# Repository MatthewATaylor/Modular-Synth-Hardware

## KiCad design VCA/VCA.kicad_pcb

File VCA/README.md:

# VCA

A simple dual VCA based on [the similar Yusynth design](http://yusynth.net/Modular/EN/VCA/index.html), including both a Eurorack level and line level output.

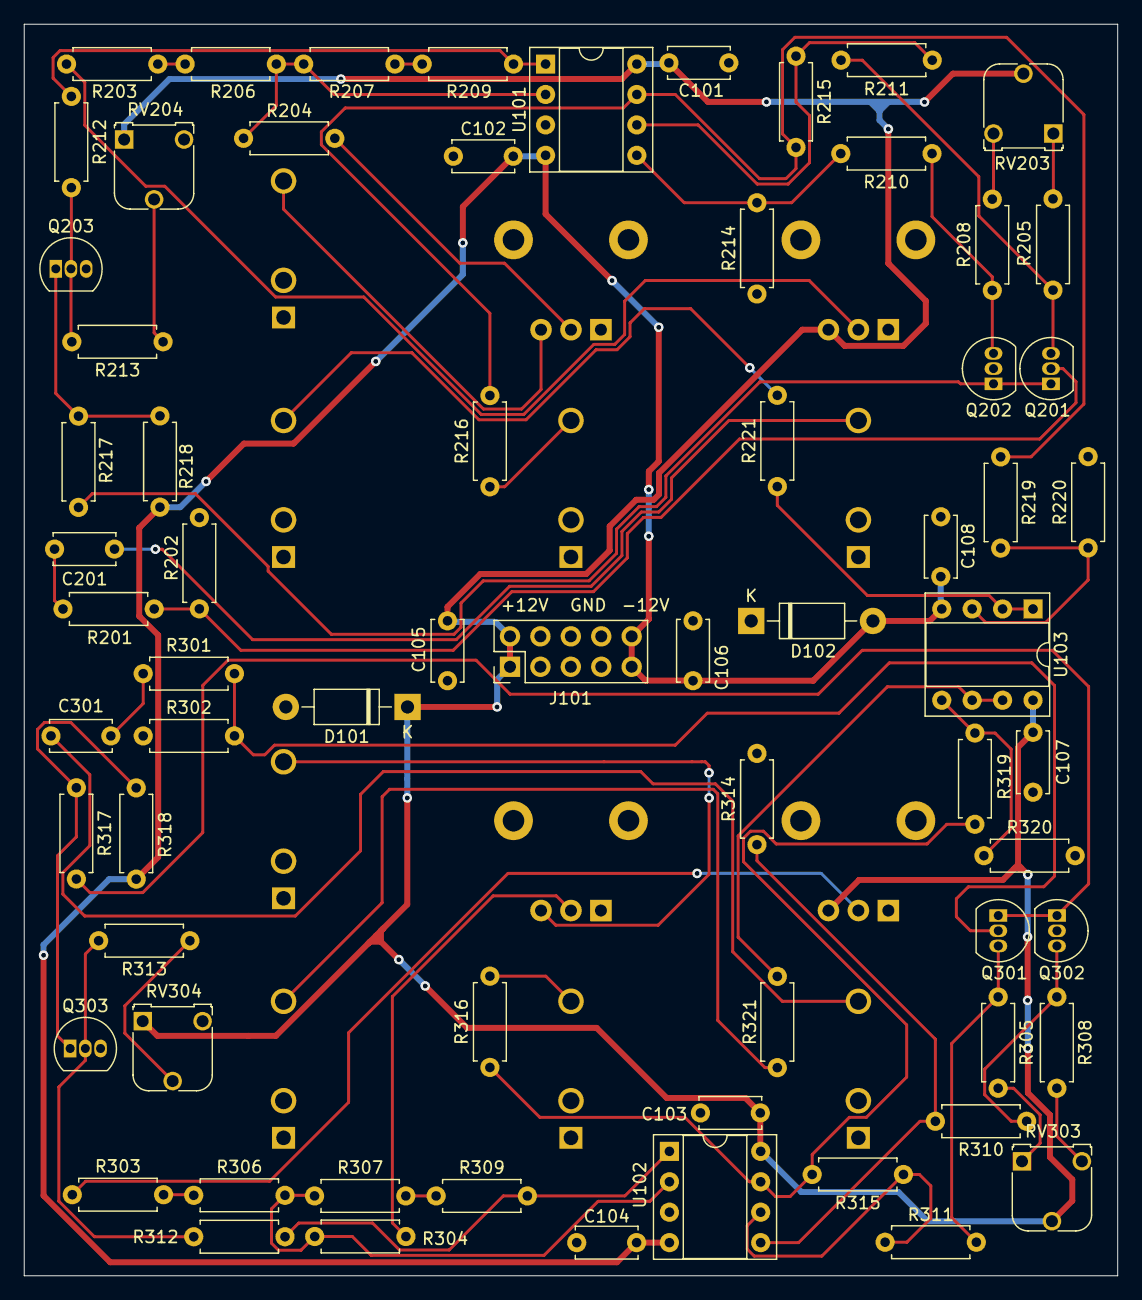
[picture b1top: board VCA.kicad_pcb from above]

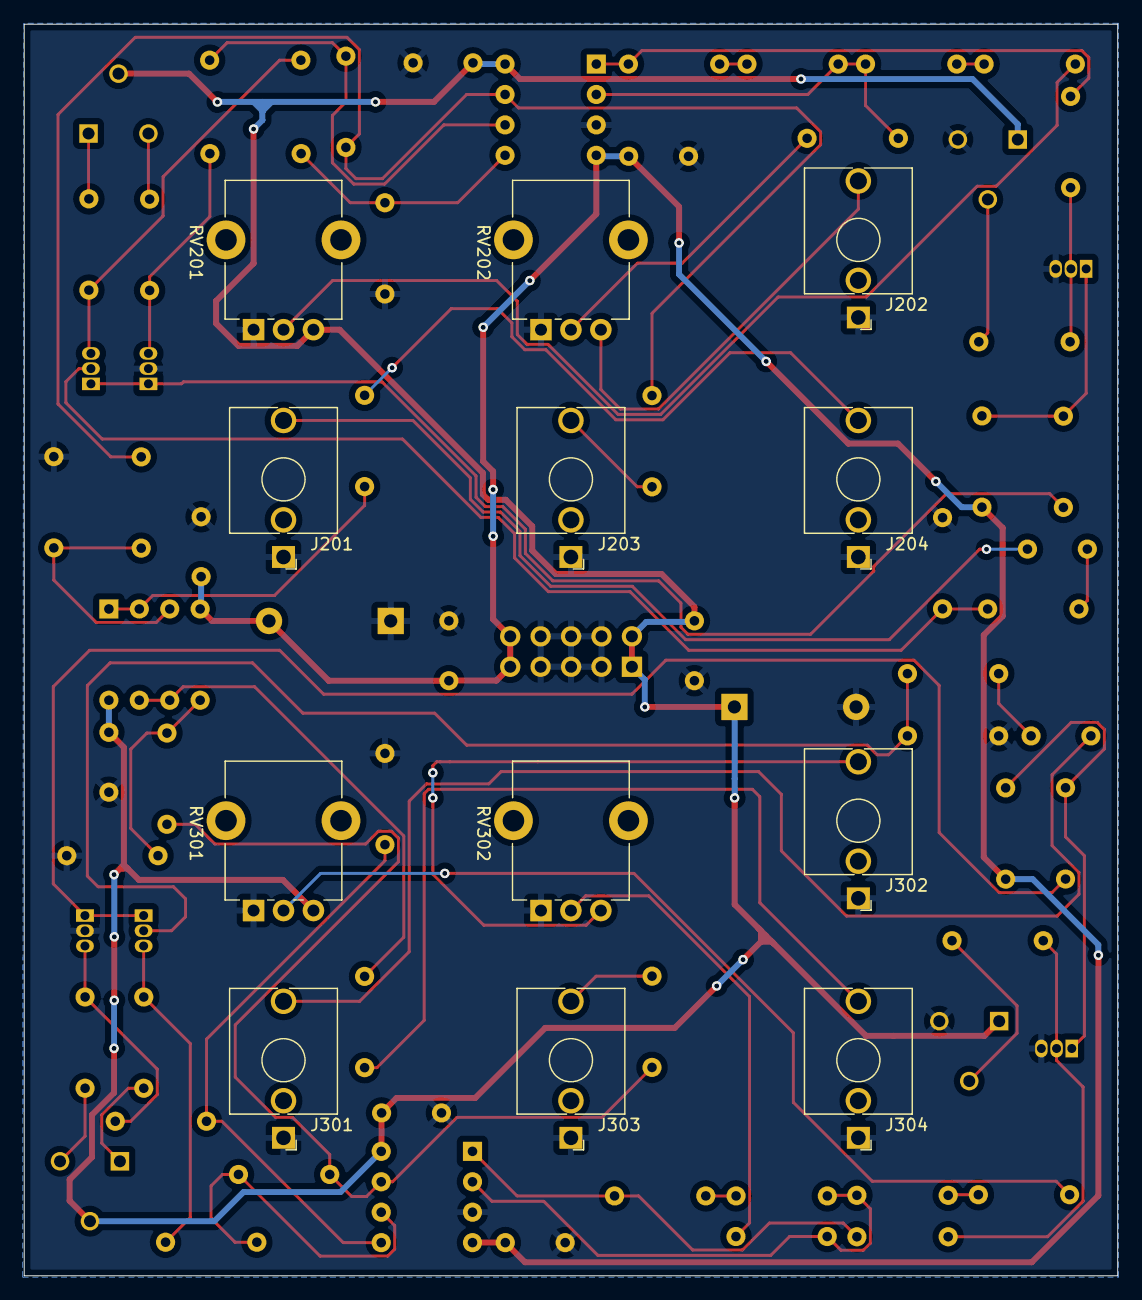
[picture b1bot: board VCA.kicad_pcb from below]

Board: 2 copper layers, 91.3 x 104.5 mm, 80 parts (12 on the bottom side), 53 nets.

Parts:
C101, C102, C103, C104, C107, C108: 10n; C_Disc_D5.0mm_W2.5mm_P5.00mm
C105, C106: 0.1u; C_Disc_D5.0mm_W2.5mm_P5.00mm
C201, C301: 10u; C_Disc_D5.0mm_W2.5mm_P5.00mm
D101, D102: 1N5819; D_DO-41_SOD81_P10.16mm_Horizontal
J101: Conn_02x05_Odd_Even; PinHeader_2x05_P2.54mm_Vertical
J201, J202, J203, J204, J301, J302, J303, J304: AudioJack2_SwitchT; Jack_3.5mm_QingPu_WQP-PJ398SM_Vertical_CircularHoles
Q201, Q202, Q203, Q301, Q302, Q303: 2N3904; TO-92_Inline
R201, R203, R301, R303: 220k; R_Axial_DIN0207_L6.3mm_D2.5mm_P7.62mm_Horizontal
R202, R216, R221, R302, R316, R321: 1k; R_Axial_DIN0207_L6.3mm_D2.5mm_P7.62mm_Horizontal
R204, R304: 470k; R_Axial_DIN0207_L6.3mm_D2.5mm_P7.62mm_Horizontal
R205, R208, R305, R308: 150k; R_Axial_DIN0207_L6.3mm_D2.5mm_P7.62mm_Horizontal
R206, R214, R215, R306, R314, R315: 330k; R_Axial_DIN0207_L6.3mm_D2.5mm_P7.62mm_Horizontal
R207, R307: 100k; R_Axial_DIN0207_L6.3mm_D2.5mm_P7.62mm_Horizontal
R209, R212, R213, R217, R309, R312, R313, R317: 22k; R_Axial_DIN0207_L6.3mm_D2.5mm_P7.62mm_Horizontal
R210, R211, R218, R310, R311, R318: 10k; R_Axial_DIN0207_L6.3mm_D2.5mm_P7.62mm_Horizontal
R219, R319: 5.6k; R_Axial_DIN0207_L6.3mm_D2.5mm_P7.62mm_Horizontal
R220, R320: 1.5k; R_Axial_DIN0207_L6.3mm_D2.5mm_P7.62mm_Horizontal
RV201, RV202, RV301, RV302: 50k; Potentiometer_Alpha_RD901F-40-00D_Single_Vertical_CircularH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
RV203, RV204, RV303, RV304: 10k; Potentiometer_Runtron_RM-065_Vertical
U101, U102, U103: TL072; DIP-8_W7.62mm_Socket

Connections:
+12V: C101.1, C103.1, C105.1, C107.1, D101.1 (K), J101.1, J101.2, RV201.3, RV203.2, RV204.1, RV301.3, RV303.2, RV304.1, U101.8 (V+), U102.8 (V+), U103.8 (V+)
-12V: C102.1, C104.1, C106.2, C108.1, D102.2 (A), J101.9, J101.10, R218.1, R318.1, U101.4 (V-), U102.4 (V-), U103.4 (V-)
GND: C101.2, C102.2, C103.2, C104.2, C105.2, C106.1, C107.2, C108.2, D101.2 (A), D102.1 (K), J101.3, J101.4, J101.5, J101.6, J101.7, J101.8, J201.S, J202.S, J203.S, J204.S, J301.S, J302.S, J303.S, J304.S, Q202.2 (B), Q203.3 (C), Q302.2 (B), Q303.3 (C), R202.1, R214.2, R220.2, R302.1, R314.2, R320.2, RV201.1, RV202.1, RV204.3, RV301.1, RV302.1, RV304.3, U101.3 (+), U102.3 (+)
unnamed: C201.1, J201.T
unnamed: C201.2, R201.1
unnamed: C301.1, J301.T
unnamed: C301.2, R301.1
unnamed: J202.T, RV202.3
unnamed: J203.T, R216.2
unnamed: J204.T, R221.2
unnamed: J302.T, RV302.3
unnamed: J303.T, R316.2
unnamed: J304.T, R321.2
unnamed: Q201.1 (E), Q202.1 (E), R217.2
unnamed: Q201.2 (B), R201.2, R202.2
unnamed: Q201.3 (C), R205.1, R211.1
unnamed: Q202.3 (C), R208.1, R210.1
unnamed: Q203.1 (E), R217.1, R218.2
unnamed: Q203.2 (B), R212.2, R213.2
unnamed: Q301.1 (E), Q302.1 (E), R317.2
unnamed: Q301.2 (B), R301.2, R302.2
unnamed: Q301.3 (C), R305.1, R311.1
unnamed: Q302.3 (C), R308.1, R310.1
unnamed: Q303.1 (E), R317.1, R318.2
unnamed: Q303.2 (B), R312.2, R313.2
unnamed: R203.1, RV201.2
unnamed: R203.2, R206.1
unnamed: R204.1, RV202.2
unnamed: R204.2, R206.2, R207.1, U101.2 (-)
unnamed: R205.2, RV203.1
unnamed: R207.2, R209.1
unnamed: R208.2, RV203.3
unnamed: R209.2, R212.1, U101.1
unnamed: R210.2, R214.1, U101.5 (+)
unnamed: R211.2, R215.1, U101.6 (-)
unnamed: R213.1, RV204.2
unnamed: R215.2, R216.1, R219.1, U101.7
unnamed: R219.2, R220.1, U103.3 (+)
unnamed: R221.1, U103.1, U103.2 (-)
unnamed: R303.1, RV301.2
unnamed: R303.2, R306.1
unnamed: R304.1, RV302.2
unnamed: R304.2, R306.2, R307.1, U102.2 (-)
unnamed: R305.2, RV303.1
unnamed: R307.2, R309.1
unnamed: R308.2, RV303.3
unnamed: R309.2, R312.1, U102.1
unnamed: R310.2, R314.1, U102.5 (+)
unnamed: R311.2, R315.1, U102.6 (-)
unnamed: R313.1, RV304.2
unnamed: R315.2, R316.1, R319.1, U102.7
unnamed: R319.2, R320.1, U103.5 (+)
unnamed: R321.1, U103.6 (-), U103.7

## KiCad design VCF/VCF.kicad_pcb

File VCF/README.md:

# VCF

A voltage-controlled low-pass filter based on Moog's transistor ladder filter, including:

* A linear to exponential converter for the inputs
* Resonance CV
* Compensation for higher resonance values leading to a lower output level

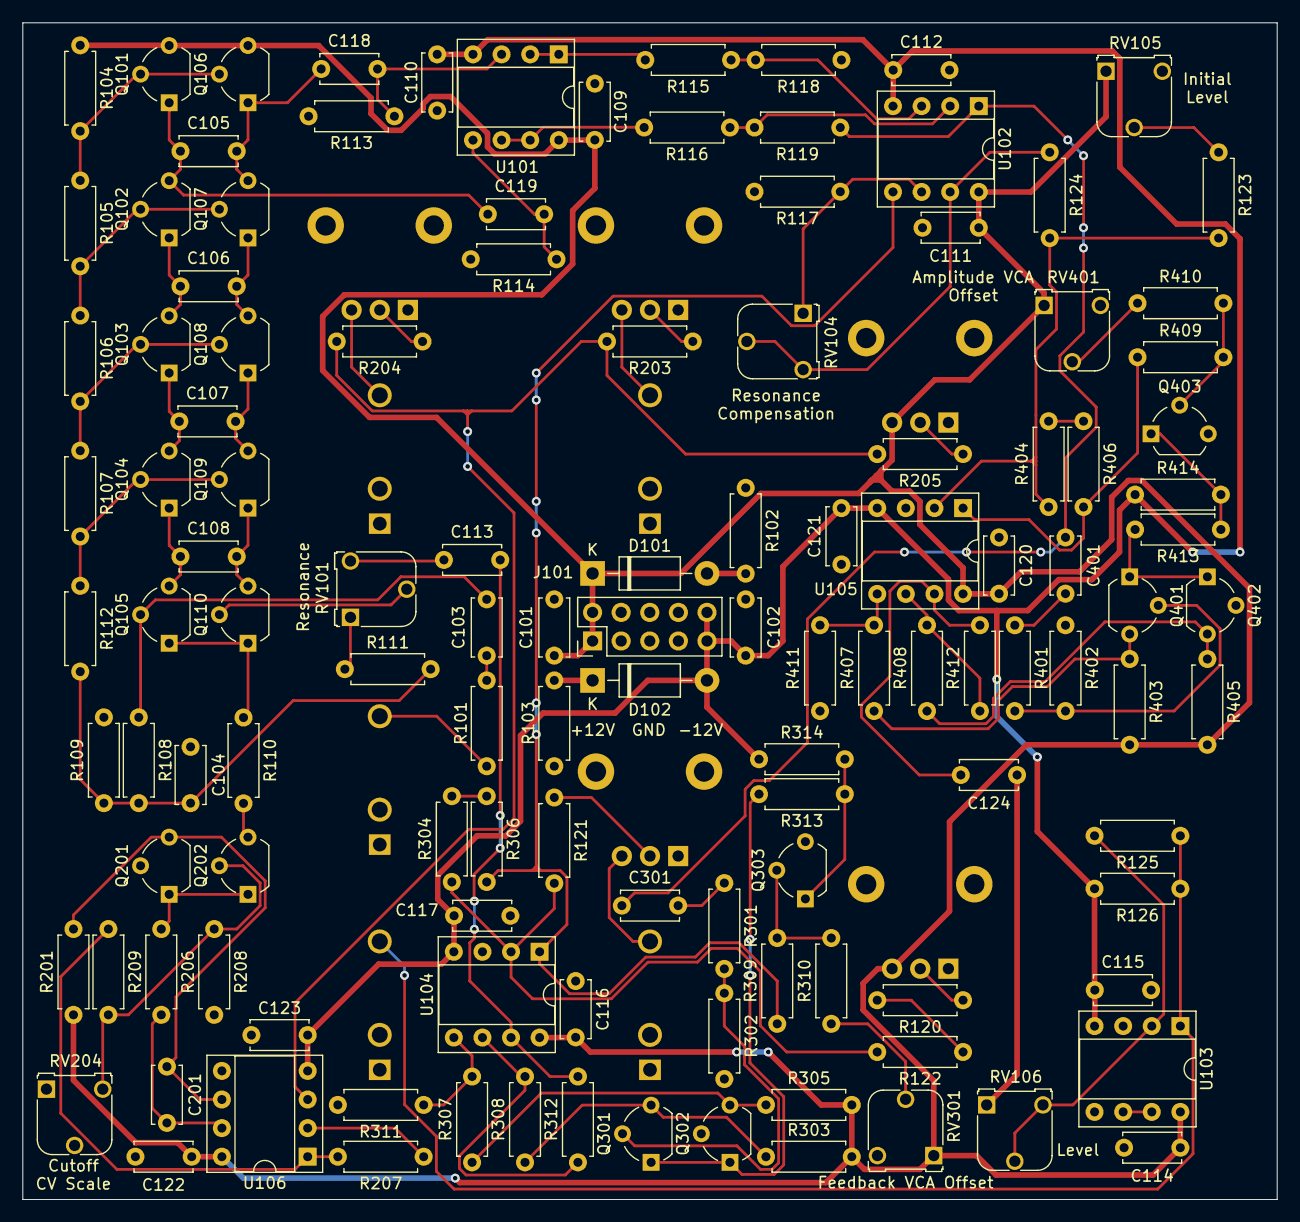
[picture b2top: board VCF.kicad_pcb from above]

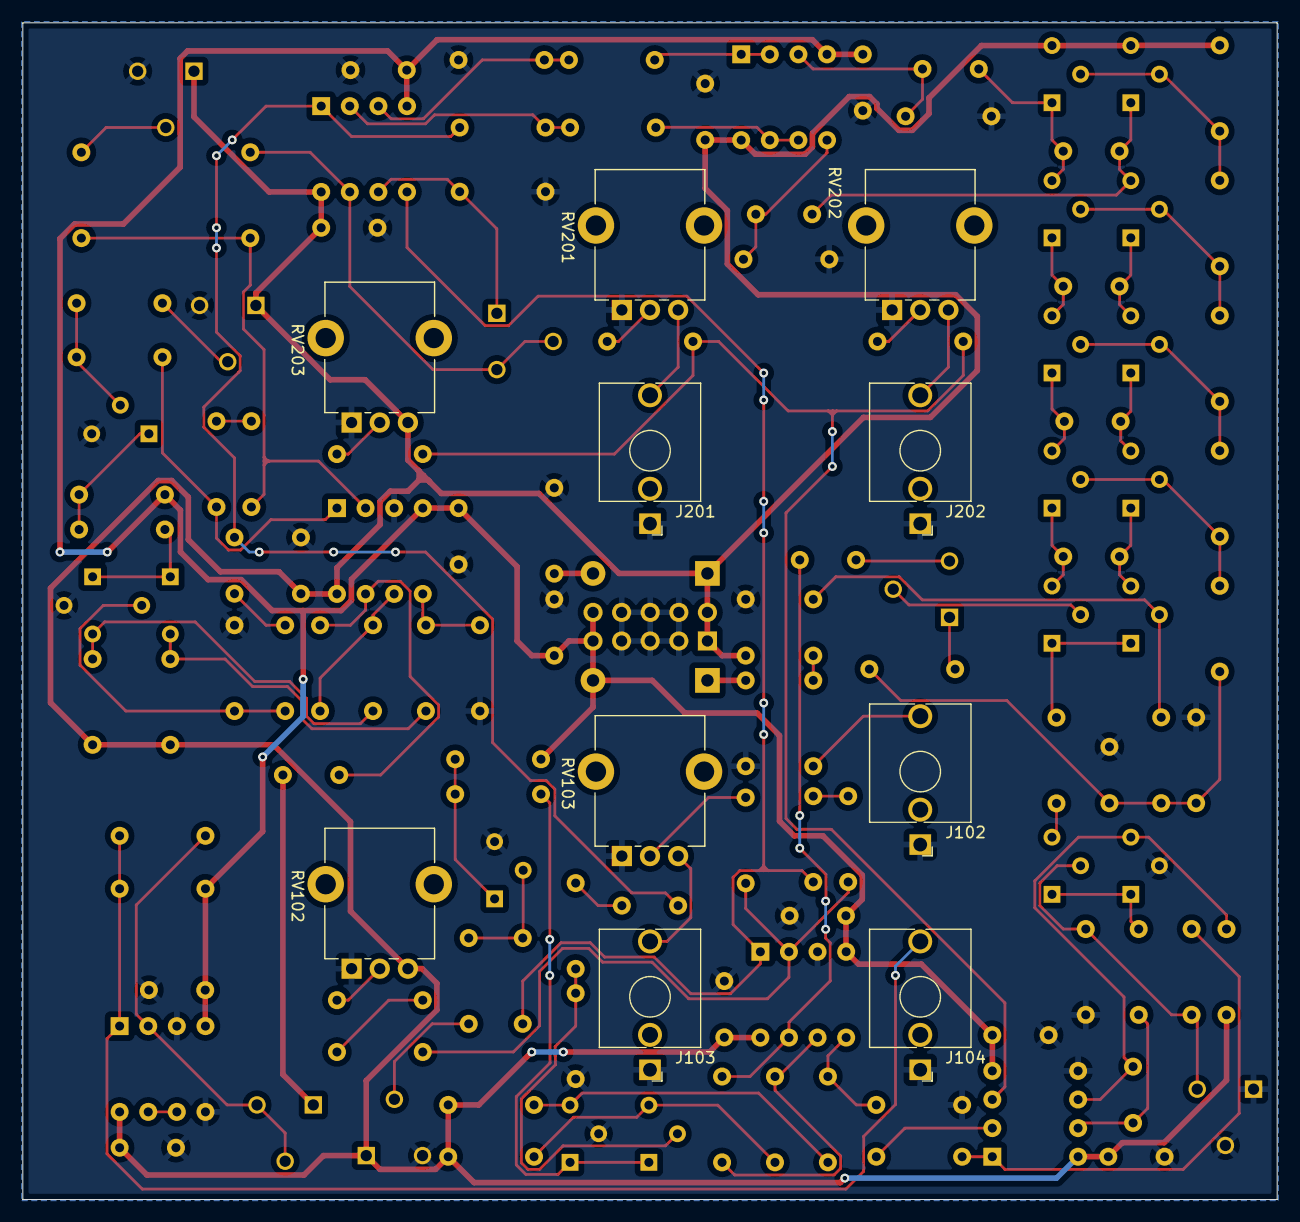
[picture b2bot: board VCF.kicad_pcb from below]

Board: 2 copper layers, 111.4 x 104.5 mm, 133 parts (10 on the bottom side), 84 nets.

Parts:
C101, C102, C113: 1u; C_Disc_D5.0mm_W2.5mm_P5.00mm
C103, C124, C301, C401: 10u; C_Disc_D5.0mm_W2.5mm_P5.00mm
C104: 220u; C_Disc_D5.0mm_W2.5mm_P5.00mm
C105, C106, C107, C108: 47n; C_Disc_D5.0mm_W2.5mm_P5.00mm
C109, C110, C111, C112, C114, C115, C116, C117, C120, C121, C122, C123: 10n; C_Disc_D5.0mm_W2.5mm_P5.00mm
C118, C119: 220n; C_Disc_D5.0mm_W2.5mm_P5.00mm
C201: 1n; C_Disc_D5.0mm_W2.5mm_P5.00mm
D101, D102: 1N5819; D_DO-41_SOD81_P10.16mm_Horizontal
J101: Conn_02x05_Odd_Even; PinHeader_2x05_P2.54mm_Vertical
J102, J103, J104, J201, J202: AudioJack2_SwitchT; Jack_3.5mm_QingPu_WQP-PJ398SM_Vertical_CircularHoles
Q101, Q102, Q103, Q104, Q105, Q106, Q107, Q108, Q109, Q110, Q201, Q202, Q301, Q302, Q303, Q401, Q402, Q403: 2N3904; TO-92_Wide
R101, R307, R308, R314, R407, R408, R414: 10k; R_Axial_DIN0207_L6.3mm_D2.5mm_P7.62mm_Horizontal
R102, R103: 10; R_Axial_DIN0207_L6.3mm_D2.5mm_P7.62mm_Horizontal
R104: 330; R_Axial_DIN0207_L6.3mm_D2.5mm_P7.62mm_Horizontal
R105, R106, R107, R112: 150; R_Axial_DIN0207_L6.3mm_D2.5mm_P7.62mm_Horizontal
R108, R208: 470; R_Axial_DIN0207_L6.3mm_D2.5mm_P7.62mm_Horizontal
R109: 220; R_Axial_DIN0207_L6.3mm_D2.5mm_P7.62mm_Horizontal
R110, R117, R206, R302, R402: 1k; R_Axial_DIN0207_L6.3mm_D2.5mm_P7.62mm_Horizontal
R111, R115, R116: 820; R_Axial_DIN0207_L6.3mm_D2.5mm_P7.62mm_Horizontal
R113, R114: 1M; R_Axial_DIN0207_L6.3mm_D2.5mm_P7.62mm_Horizontal
R118, R119, R209: 8.2k; R_Axial_DIN0207_L6.3mm_D2.5mm_P7.62mm_Horizontal
R120, R124, R301, R401: 220k; R_Axial_DIN0207_L6.3mm_D2.5mm_P7.62mm_Horizontal
R121: 470k; R_Axial_DIN0207_L6.3mm_D2.5mm_P7.62mm_Horizontal
R122, R311, R312, R411, R412: 330k; R_Axial_DIN0207_L6.3mm_D2.5mm_P7.62mm_Horizontal
R123: 75k; R_Axial_DIN0207_L6.3mm_D2.5mm_P7.62mm_Horizontal
R125: 68k; R_Axial_DIN0207_L6.3mm_D2.5mm_P7.62mm_Horizontal
R126: 1.5k; R_Axial_DIN0207_L6.3mm_D2.5mm_P7.62mm_Horizontal
R201: 4.7M; R_Axial_DIN0207_L6.3mm_D2.5mm_P7.62mm_Horizontal
R203, R204, R205, R304, R404: 100k; R_Axial_DIN0207_L6.3mm_D2.5mm_P7.62mm_Horizontal
R207, R306, R309, R310, R313, R406, R409, R410, R413: 22k; R_Axial_DIN0207_L6.3mm_D2.5mm_P7.62mm_Horizontal
R303, R305, R403, R405: 150k; R_Axial_DIN0207_L6.3mm_D2.5mm_P7.62mm_Horizontal
RV101, RV104, RV105, RV106, RV204, RV301, RV401: 10k; Potentiometer_Runtron_RM-065_Vertical_Improved
RV102, RV103, RV201, RV202, RV203: 50k; Potentiometer_Alpha_RD901F-40-00D_Single_Vertical_CircularH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
U101, U102, U103, U104, U105, U106: TL072; DIP-8_W7.62mm_Socket

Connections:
+12V: C101.1, C109.1, C111.1, C114.1, C116.1, C120.1, C122.1, D101.1 (K), J101.1, J101.2, Q101.3 (C), Q106.3 (C), R104.1, R201.1, R303.2, R305.2, R403.2, R405.2, RV102.3, RV105.1, RV203.3, RV301.1, RV401.1, U101.8 (V+), U102.8 (V+), U103.8 (V+), U104.8 (V+), U105.8 (V+), U106.8 (V+)
-12V: C102.2, C110.1, C112.1, C115.1, C117.1, C121.1, C123.1, D102.2 (A), J101.9, J101.10, R126.2, R314.1, R414.1, U101.4 (V-), U102.4 (V-), U103.4 (V-), U104.4 (V-), U105.4 (V-), U106.4 (V-)
/Amplitude VCA/CV: R123.2, R124.2, R404.1, U105.2 (-)
/Amplitude VCA/In: C301.1, C401.1, R119.1, U102.1
/Amplitude VCA/Out: C124.2, R412.2, U105.7
/Control/CurrentSink: Q202.3 (C), R110.2
/Feedback VCA/CV: R121.2, R122.2, R304.1, U104.2 (-)
/Feedback VCA/CVSum: R306.2, R309.1, U102.5 (+), U104.1
/Feedback VCA/Out: C113.2, R312.2, U104.7
GND: C101.2, C102.1, C104.1, C109.2, C110.2, C111.2, C112.2, C114.2, C115.2, C116.2, C117.2, C120.2, C121.2, C122.2, C123.2, J101.3, J101.4, J101.5, J101.6, J101.7, J101.8, J102.S, J103.S, J104.S, J201.S, J202.S, Q201.2 (B), Q302.2 (B), Q303.3 (C), Q402.2 (B), Q403.3 (C), R102.1, R103.2, R109.2, R113.2, R114.2, R117.2, R118.1, R208.2, R302.1, R311.2, R402.1, R411.2, RV102.1, RV103.1, RV105.3, RV201.1, RV202.1, RV203.1, RV204.1, RV204.2, RV301.3, RV401.3, U103.3 (+), U103.5 (+), U104.3 (+), U105.3 (+), U106.5 (+)
unnamed: C103.1, R101.1
unnamed: C103.2, Q105.2 (B), R108.1
unnamed: C104.2, R108.2, R109.1, R111.2, R112.2
unnamed: C105.1, C119.1, Q101.1 (E), Q102.3 (C)
unnamed: C105.2, C118.1, Q106.1 (E), Q107.3 (C)
unnamed: C106.1, Q102.1 (E), Q103.3 (C)
unnamed: C106.2, Q107.1 (E), Q108.3 (C)
unnamed: C107.1, Q103.1 (E), Q104.3 (C)
unnamed: C107.2, Q108.1 (E), Q109.3 (C)
unnamed: C108.1, Q104.1 (E), Q105.3 (C)
unnamed: C108.2, Q109.1 (E), Q110.3 (C)
unnamed: C113.1, RV101.3
unnamed: C118.2, R113.1, U101.3 (+)
unnamed: C119.2, R114.1, U101.5 (+)
unnamed: C124.1, RV106.1
unnamed: C201.1, Q201.3 (C), R201.2, U106.6 (-)
unnamed: C201.2, R206.2, U106.7
unnamed: C301.2, R301.1
unnamed: C401.2, R401.1
unnamed: D101.2 (A), R102.2
unnamed: D102.1 (K), R103.1
unnamed: J102.T, R101.2
unnamed: J103.T, RV103.3
unnamed: J104.T, R125.1, R126.1, U103.1
unnamed: J201.T, RV201.3
unnamed: J202.T, RV202.3
unnamed: Q101.2 (B), Q106.2 (B), R104.2, R105.1
unnamed: Q102.2 (B), Q107.2 (B), R105.2, R106.1
unnamed: Q103.2 (B), Q108.2 (B), R106.2, R107.1
unnamed: Q104.2 (B), Q109.2 (B), R107.2, R112.1
unnamed: Q105.1 (E), Q110.1 (E), R110.1
unnamed: Q110.2 (B), RV101.2
unnamed: Q201.1 (E), Q202.1 (E), R206.1
unnamed: Q202.2 (B), R208.1, R209.2, RV204.3
unnamed: Q301.1 (E), Q302.1 (E), R313.2
unnamed: Q301.2 (B), R301.2, R302.2
unnamed: Q301.3 (C), R303.1, R308.1
unnamed: Q302.3 (C), R305.1, R307.1
unnamed: Q303.1 (E), R313.1, R314.2
unnamed: Q303.2 (B), R309.2, R310.2
unnamed: Q401.1 (E), Q402.1 (E), R413.2
unnamed: Q401.2 (B), R401.2, R402.2
unnamed: Q401.3 (C), R403.1, R407.1
unnamed: Q402.3 (C), R405.1, R408.1
unnamed: Q403.1 (E), R413.1, R414.2
unnamed: Q403.2 (B), R409.2, R410.2
unnamed: R111.1, RV101.1
unnamed: R115.1, R118.2, U102.3 (+)
unnamed: R115.2, U101.1, U101.2 (-)
unnamed: R116.1, R119.2, U102.2 (-)
unnamed: R116.2, U101.6 (-), U101.7
unnamed: R117.1, RV104.1, U102.6 (-)
unnamed: R120.1, RV102.2
unnamed: R120.2, R122.1
unnamed: R121.1, RV103.2
unnamed: R123.1, RV105.2
unnamed: R124.1, RV104.2, RV104.3, U102.7
unnamed: R125.2, RV106.2, RV106.3, U103.2 (-)
unnamed: R203.1, RV201.2
unnamed: R203.2, R204.2, R205.2, U106.3 (+)
unnamed: R204.1, RV202.2
unnamed: R205.1, RV203.2
unnamed: R207.1, U106.2 (-)
unnamed: R207.2, R209.1, U106.1
unnamed: R304.2, R306.1
unnamed: R307.2, R311.1, U104.5 (+)
unnamed: R308.2, R312.1, U104.6 (-)
unnamed: R310.1, RV301.2
unnamed: R404.2, R406.1
unnamed: R406.2, R409.1, U105.1
unnamed: R407.2, R411.1, U105.5 (+)
unnamed: R408.2, R412.1, U105.6 (-)
unnamed: R410.1, RV401.2
unnamed: U103.6 (-), U103.7

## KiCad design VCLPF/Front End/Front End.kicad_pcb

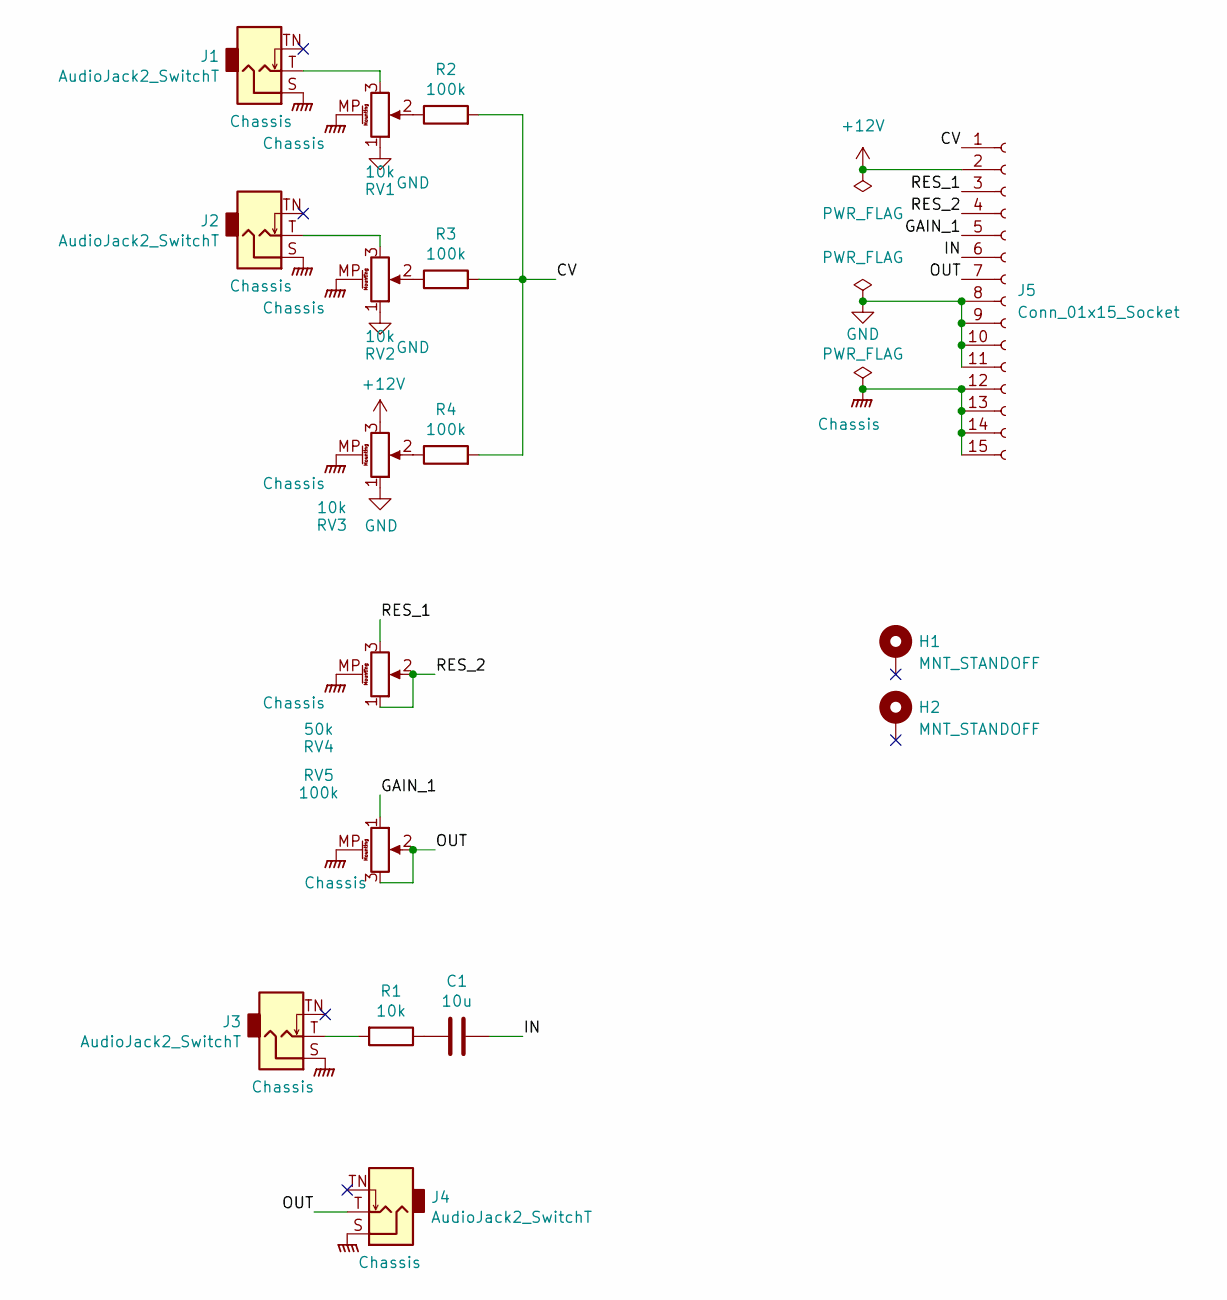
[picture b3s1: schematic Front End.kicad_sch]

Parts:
C1: 10u; C_Disc_D5.5mm_W4.0mm_P2.50mm
H1, H2: MNT_STANDOFF; MountingHole_Pitch7.5mm_Drill3.4mm
J1, J2, J3, J4: AudioJack2_SwitchT; Jack_3.5mm_QingPu_WQP-PJ398SM_Vertical_CircularHoles
J5: Conn_01x15_Socket; PinHeader_1x15_P2.54mm_Vertical
R1: 10k; R_Axial_DIN0207_L6.3mm_D2.5mm_P7.62mm_Horizontal
R2, R3, R4: 100k; R_Axial_DIN0207_L6.3mm_D2.5mm_P7.62mm_Horizontal
RV1, RV2, RV3: 10k; Potentiometer_Alpha_RD901F-40-00D_Single_Vertical_MP
RV4: 50k; Potentiometer_Alpha_RD901F-40-00D_Single_Vertical_MP
RV5: 100k; Potentiometer_Alpha_RD901F-40-00D_Single_Vertical_MP

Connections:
+12V: J5.2, RV3.3
/CV: J5.1, R2.2, R3.2, R4.2
/GAIN_1: J5.5, RV5.1
/IN: C1.2, J5.6
/OUT: J4.T, J5.7, RV5.2, RV5.3
/RES_1: J5.3, RV4.3
/RES_2: J5.4, RV4.1, RV4.2
Chassis: J1.S, J2.S, J3.S, J4.S, J5.12, J5.13, J5.14, J5.15, RV1.MP (MountPin), RV2.MP (MountPin), RV3.MP (MountPin), RV4.MP (MountPin), RV5.MP (MountPin)
GND: J5.8, J5.9, J5.10, J5.11, RV1.1, RV2.1, RV3.1
unnamed: C1.1, R1.1
unnamed: J1.T, RV1.3
unnamed: J2.T, RV2.3
unnamed: J3.T, R1.2
unnamed: R2.1, RV1.2
unnamed: R3.1, RV2.2
unnamed: R4.1, RV3.2

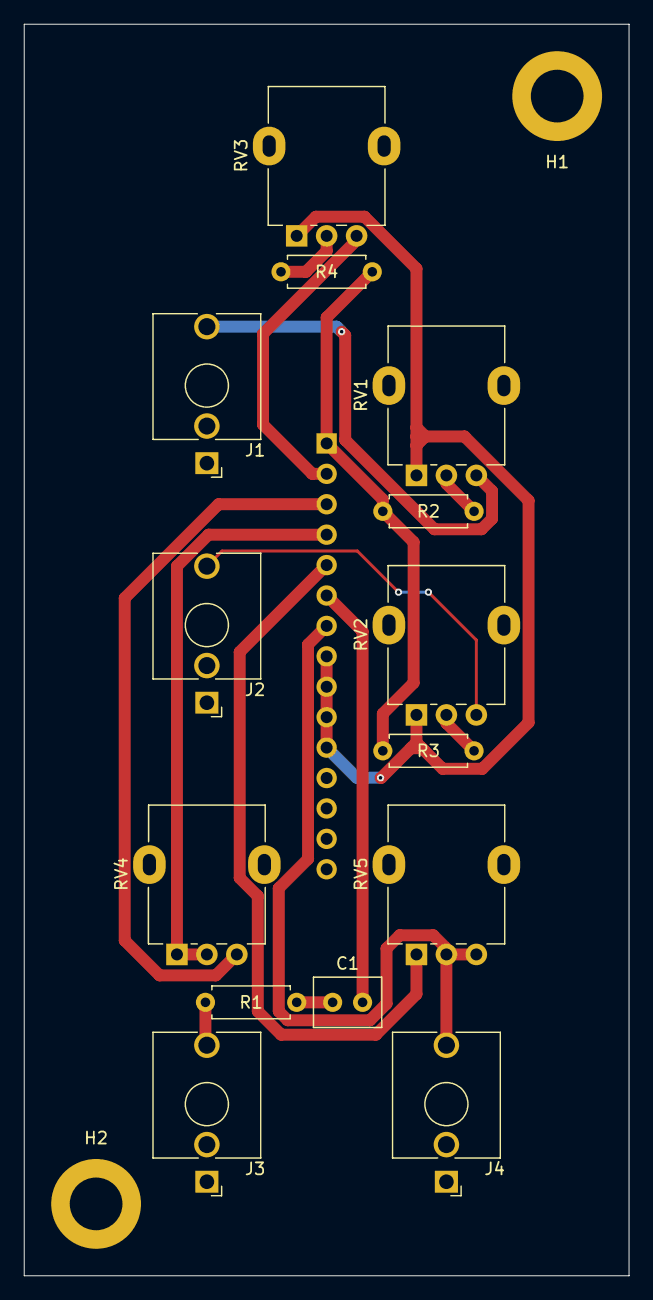
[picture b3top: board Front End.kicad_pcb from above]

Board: 2 copper layers, 50.5 x 104.5 mm, 17 parts (1 on the bottom side), 16 nets.

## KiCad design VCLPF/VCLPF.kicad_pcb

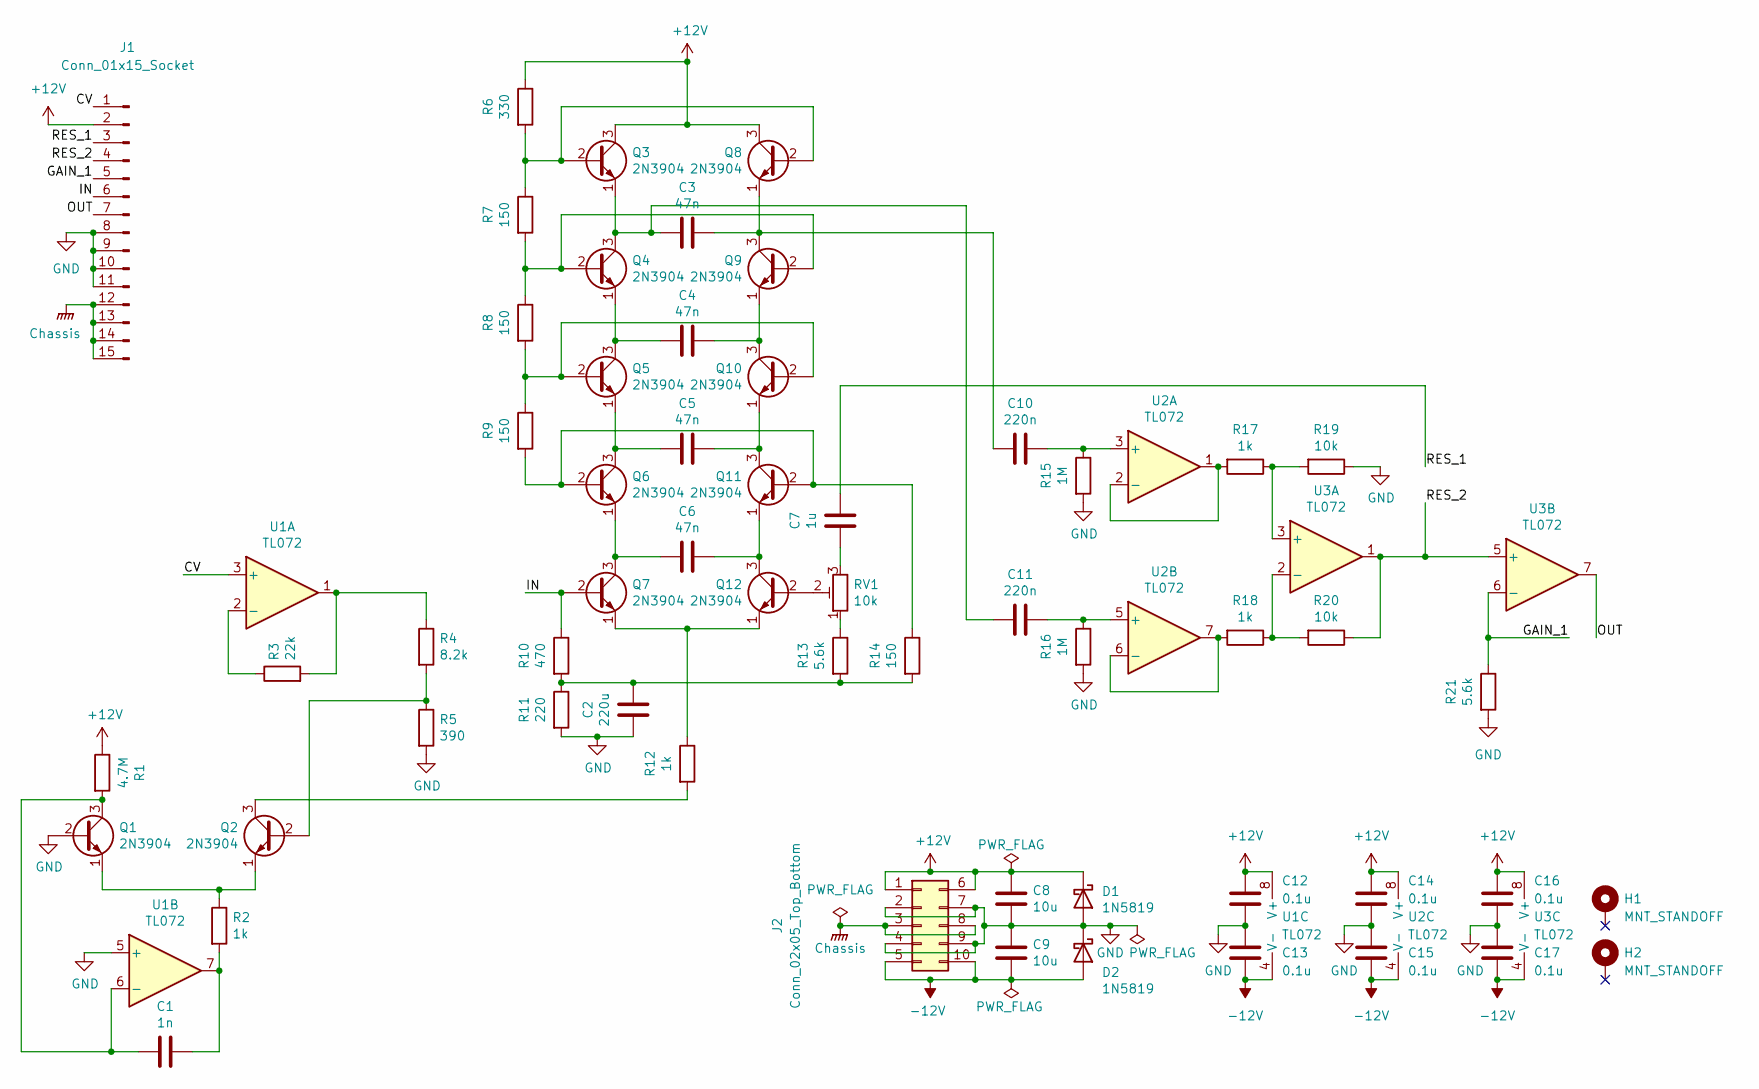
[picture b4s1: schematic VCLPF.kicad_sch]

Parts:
C1: 1n; C_Disc_D5.5mm_W2.5mm_P2.50mm
C2: 220u; CP_Radial_D10.0mm_P5.00mm
C3, C4, C5, C6: 47n; C_Disc_D5.5mm_W2.5mm_P2.50mm
C7: 1u; C_Disc_D5.5mm_W4.0mm_P2.50mm
C8, C9: 10u; C_Disc_D5.5mm_W4.0mm_P2.50mm
C10, C11: 220n; C_Disc_D5.5mm_W2.5mm_P2.50mm
C12, C13, C14, C15, C16, C17: 0.1u; C_Disc_D5.5mm_W2.5mm_P2.50mm
D1, D2: 1N5819; D_DO-41_SOD81_P10.16mm_Horizontal
H1, H2: MNT_STANDOFF; MountingHole_Pitch7.5mm_Drill3.4mm
J1: Conn_01x15_Socket; PinHeader_1x15_P2.54mm_Vertical
J2: Conn_02x05_Top_Bottom; Molex_Mini-Fit_Jr_5566-10A_2x05_P4.20mm_Vertical
Q1, Q2, Q3, Q4, Q5, Q6, Q7, Q8, Q9, Q10, Q11, Q12: 2N3904; TO-92_HandSolder
R1: 4.7M; R_Axial_DIN0207_L6.3mm_D2.5mm_P7.62mm_Horizontal
R2, R12, R17, R18: 1k; R_Axial_DIN0207_L6.3mm_D2.5mm_P7.62mm_Horizontal
R3: 22k; R_Axial_DIN0207_L6.3mm_D2.5mm_P7.62mm_Horizontal
R4: 8.2k; R_Axial_DIN0207_L6.3mm_D2.5mm_P7.62mm_Horizontal
R5: 390; R_Axial_DIN0207_L6.3mm_D2.5mm_P7.62mm_Horizontal
R6: 330; R_Axial_DIN0207_L6.3mm_D2.5mm_P7.62mm_Horizontal
R7, R8, R9, R14: 150; R_Axial_DIN0207_L6.3mm_D2.5mm_P7.62mm_Horizontal
R10: 470; R_Axial_DIN0207_L6.3mm_D2.5mm_P7.62mm_Horizontal
R11: 220; R_Axial_DIN0207_L6.3mm_D2.5mm_P7.62mm_Horizontal
R13, R21: 5.6k; R_Axial_DIN0207_L6.3mm_D2.5mm_P7.62mm_Horizontal
R15, R16: 1M; R_Axial_DIN0207_L6.3mm_D2.5mm_P7.62mm_Horizontal
R19, R20: 10k; R_Axial_DIN0207_L6.3mm_D2.5mm_P7.62mm_Horizontal
RV1: 10k; Potentiometer_Runtron_RM-065_Vertical
U1, U2, U3: TL072; DIP-8_W7.62mm_Socket

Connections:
+12V: C8.1, C12.2, C14.2, C16.2, D1.1 (K), J1.2, J2.1, J2.6, Q3.3 (C), Q8.3 (C), R1.1, R6.1, U1.8 (V+), U2.8 (V+), U3.8 (V+)
-12V: C9.2, C13.1, C15.1, C17.1, D2.2 (A), J2.5, J2.10, U1.4 (V-), U2.4 (V-), U3.4 (V-)
/CV: J1.1, U1.3 (+)
/GAIN_1: J1.5, R21.1, U3.6 (-)
/IN: J1.6, Q7.2 (B), R10.1
/OUT: J1.7, U3.7
/RES_1: C7.2, J1.3
/RES_2: J1.4, R20.1, U3.1, U3.5 (+)
Chassis: J1.12, J1.13, J1.14, J1.15, J2.3, J2.8
GND: C2.1, C8.2, C9.1, C12.1, C13.2, C14.1, C15.2, C16.1, C17.2, D1.2 (A), D2.1 (K), J1.8, J1.9, J1.10, J1.11, J2.2, J2.4, J2.7, J2.9, Q1.2 (B), R5.2, R11.2, R15.2, R16.2, R19.1, R21.2, U1.5 (+)
unnamed: C1.2, R2.2, U1.7
unnamed: C2.2, R10.2, R11.1, R13.2, R14.2
unnamed: C7.1, RV1.3
unnamed: C1.1, Q1.3 (C), R1.2, U1.6 (-)
unnamed: Q1.1 (E), Q2.1 (E), R2.1
unnamed: Q2.2 (B), R4.2, R5.1
unnamed: Q2.3 (C), R12.2
unnamed: Q3.2 (B), Q8.2 (B), R6.2, R7.1
unnamed: C3.1, C11.1, Q3.1 (E), Q4.3 (C)
unnamed: Q4.2 (B), Q9.2 (B), R7.2, R8.1
unnamed: C4.1, Q4.1 (E), Q5.3 (C)
unnamed: C5.1, Q5.1 (E), Q6.3 (C)
unnamed: C6.1, Q6.1 (E), Q7.3 (C)
unnamed: C3.2, C10.1, Q8.1 (E), Q9.3 (C)
unnamed: Q5.2 (B), Q10.2 (B), R8.2, R9.1
unnamed: C4.2, Q9.1 (E), Q10.3 (C)
unnamed: C5.2, Q10.1 (E), Q11.3 (C)
unnamed: Q6.2 (B), Q11.2 (B), R9.2, R14.1
unnamed: C6.2, Q11.1 (E), Q12.3 (C)
unnamed: Q12.2 (B), RV1.2
unnamed: Q7.1 (E), Q12.1 (E), R12.1
unnamed: R3.2, R4.1, U1.1
unnamed: R13.1, RV1.1
unnamed: R3.1, U1.2 (-)
unnamed: C10.2, R15.1, U2.3 (+)
unnamed: R17.2, U2.1, U2.2 (-)
unnamed: C11.2, R16.1, U2.5 (+)
unnamed: R18.2, U2.6 (-), U2.7
unnamed: R17.1, R19.2, U3.3 (+)
unnamed: R18.1, R20.2, U3.2 (-)

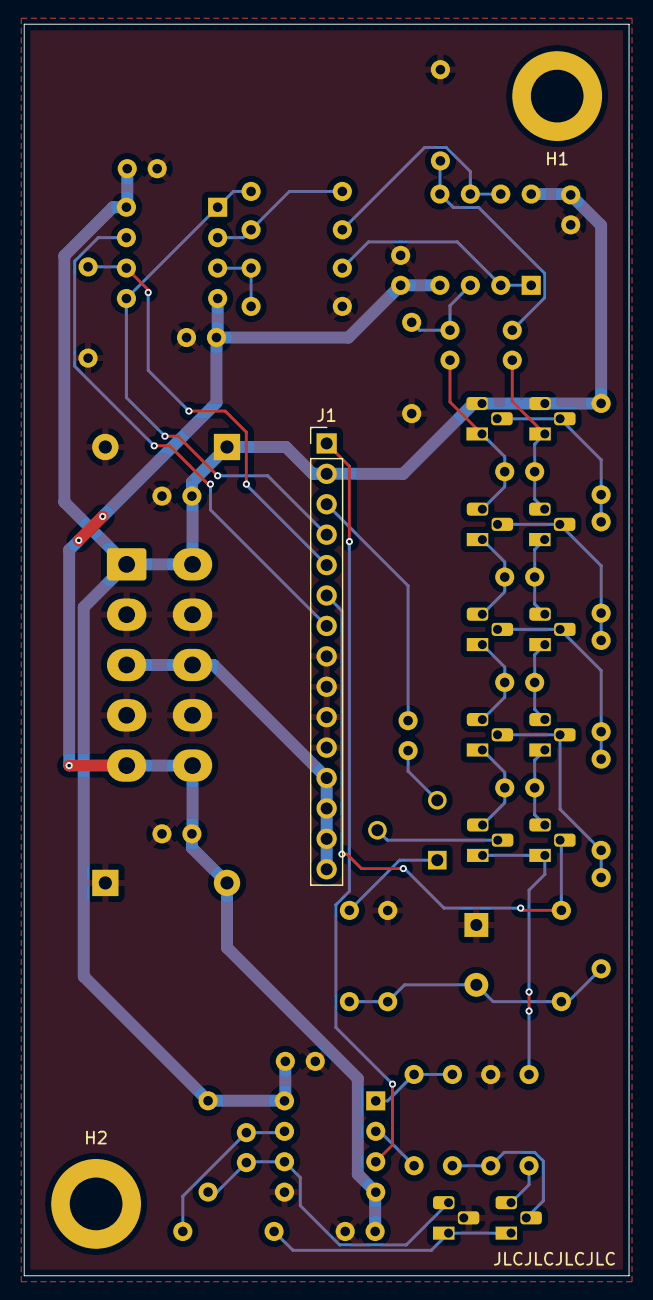
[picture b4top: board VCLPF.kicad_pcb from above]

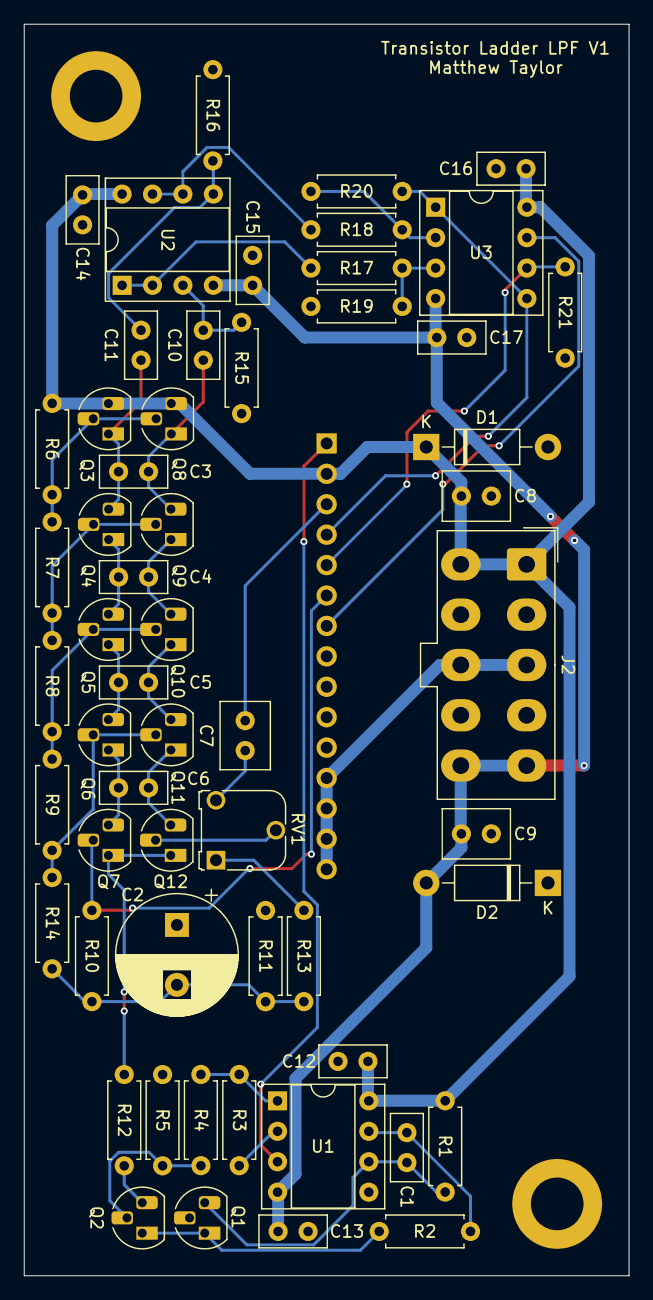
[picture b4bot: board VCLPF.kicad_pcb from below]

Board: 2 copper layers, 50.5 x 104.5 mm, 60 parts (57 on the bottom side), 40 nets.
